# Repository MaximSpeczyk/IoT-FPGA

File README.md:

# Team-H
Advanced Embedded Systems: Smart Greenhouse (Mqtt server and multiple notes)

Hardware Engineering: Vending machine (PCB design, VHDL programm)

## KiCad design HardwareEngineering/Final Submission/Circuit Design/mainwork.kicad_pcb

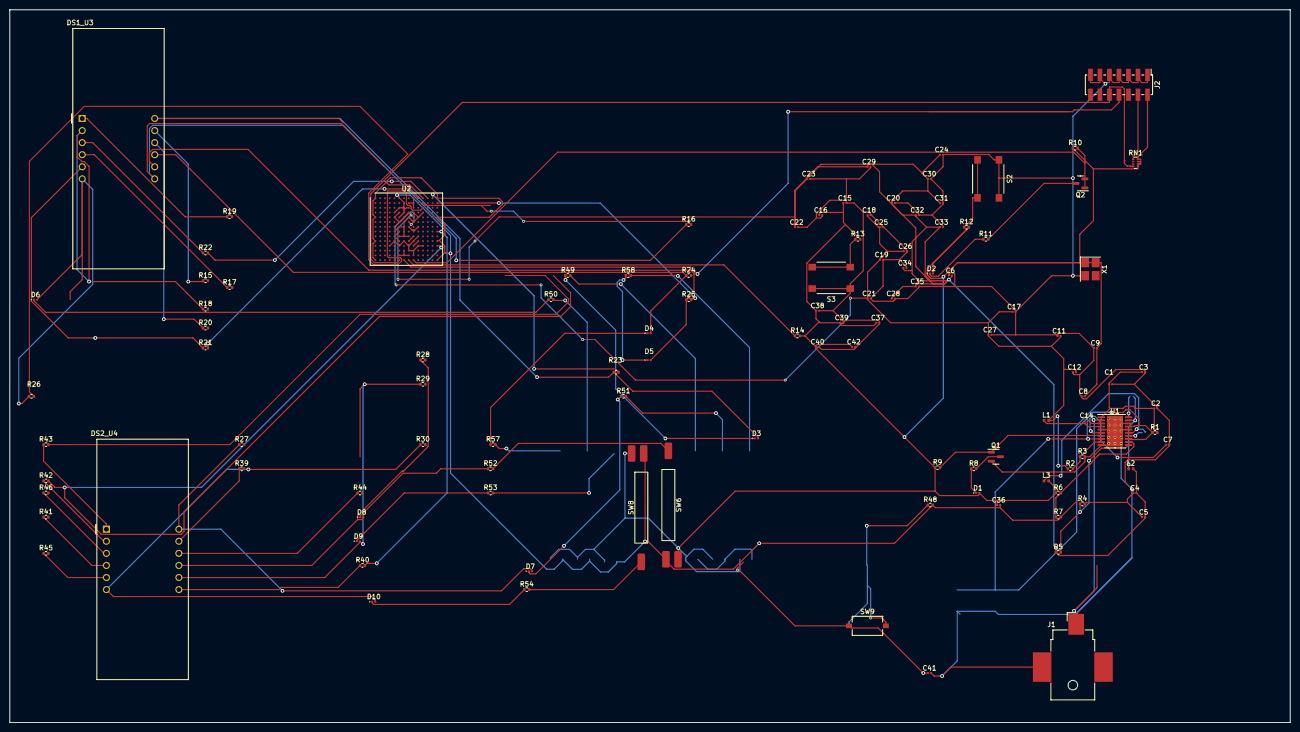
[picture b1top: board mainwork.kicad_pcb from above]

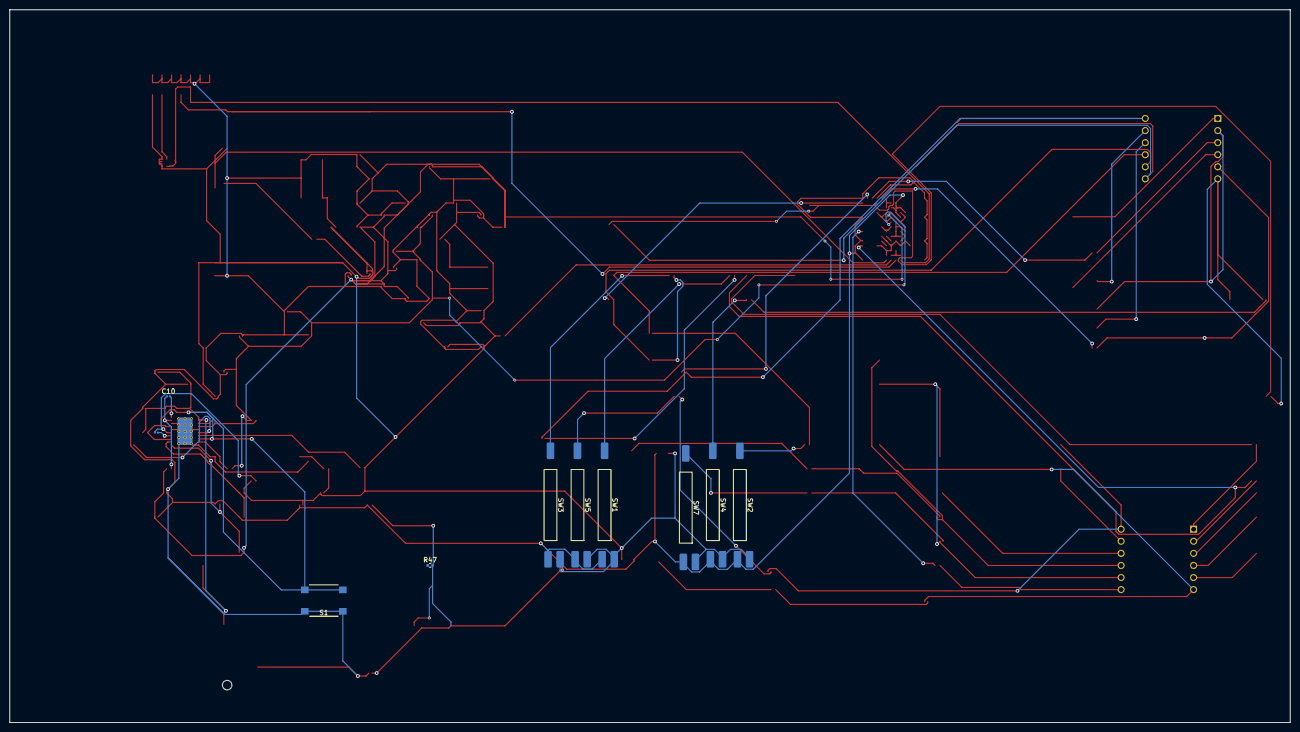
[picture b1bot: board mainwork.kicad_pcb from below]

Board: 2 copper layers, 269.2 x 149.9 mm, 125 parts (10 on the bottom side), 96 nets.

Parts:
C1, C2, C3: 10 µF; C_0201_0603Metric
C4, C5, C6, C8, C9, C11, C12: 22 µF; C_0201_0603Metric
C7: 1 µF; C_0201_0603Metric
C10, C13, C14, C15, C17, C18: 0.1 µF; C_0201_0603Metric
C16, C19, C20, C36: 47 µF; C_0201_0603Metric
C21, C22, C23, C24, C34, C37, C42: 4.7 µF; C_0201_0603Metric
C25, C26, C27, C28, C29, C30, C31, C32, C35, C38, C39, C40, C41: 0.47 µF; C_0201_0603Metric
C33: 100 µF; C_0201_0603Metric
D1, D2, D3, D4, D5, D6, D7, D8, D9, D10: LED; LED_0201_0603Metric
DS1_U3, DS2_U4: CA56-12CGKWA
J1: Barrel_Jack_Switch; BarrelJack_CUI_PJ-036AH-SMT_Horizontal
J2: XILINX_JTAG; PinHeader_2x07_P2.00mm_Vertical_SMD
L1, L3: 2.2 µH; L_0402_1005Metric
L2: 2.2 µF; L_0402_1005Metric
Q1, Q2: DMN2041L; SOT-23
R1, R9: 100K; R_0402_1005Metric
R2: 3.0K; R_0402_1005Metric
R3, R4, R7: 2.2K; R_0402_1005Metric
R5, R8, R11: 680; R_0402_1005Metric
R6: 7.36K; R_0402_1005Metric
R10, R15, R16, R17, R18, R19, R20, R21, R22, R23, R24, R25, R26, R27, R28, R29, R30, R39, R40, R41, R42, R43, R44, R45, R46, R47, R48, R49, R50, R51, R52, R53, R54, R57, R58: 330; R_0402_1005Metric
R12, R13, R14: 4.75K; R_0402_1005Metric
RN1: 10K; R_Array_Convex_4x0402
S1, S2, S3: B3FS_1010P
SW1, SW2, SW3, SW4, SW5, SW6, SW7, SW8: SW_Push_SPDT; SW_SPDT_REED_MSDM-DT
SW9: SW_SPST; SW_Tactile_SPST_NO_Straight_CK_PTS636Sx25SMTRLFS
U1: TPS65581; HTSSOP-20-1EP_4.4x6.5mm_P0.65mm_EP3.4x6.5mm_Mask2.75x3.43mm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
U2: XC7S50-FTGB196; Xilinx_FTGB196
X1: DSC61XX; Oscillator_SMD_Abracon_ASE-4Pin_3.2x2.5mm_HandSoldering

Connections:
+1V0: C4.2, C5.2, C6.2, C20.1, C22.1, C23.1, C24.1, C28.1, C29.1, C30.1, C31.1, C32.1, C33.1, C34.1, C35.1, L2.2, R5.1, U2.D6 (VCCINT), U2.D8 (VCCINT), U2.E5 (VCCBRAM), U2.E7 (VCCINT), U2.E9 (VCCINT), U2.F6 (VCCINT), U2.G5 (VCCBRAM), U2.G9 (VCCINT), U2.H6 (VCCINT), U2.J5 (VCCBRAM), U2.J9 (VCCINT), U2.K6 (VCCINT), U2.K8 (VCCINT)
+1V8A: C11.2, C12.2, C17.1, C18.1, C19.1, C21.1, C25.1, C26.1, C27.1, L1.2, R2.1, U2.F8 (VCCADC_0), U2.F10 (VCCAUX), U2.H8 (VREFP_0), U2.H10 (VCCAUX), U2.K10 (VCCAUX), U2.L9 (VCCAUX)
+3V3: C8.2, C9.2, C15.1, C16.1, C36.1, C37.1, C38.1, C39.1, C40.1, C41.1, C42.1, D1.2 (A), D2.2 (A), J2.2 (VREF), L3.2, R6.1, R9.1, R10.1, R12.2, R13.2, R14.2, RN1.5 (R4.2), RN1.6 (R3.2), RN1.7 (R2.2), RN1.8 (R1.2), SW1.1 (A), SW2.1 (A), SW3.1 (A), SW4.1 (A), SW5.1 (A), SW6.1 (A), SW7.1 (A), SW8.1 (A), SW9.1 (A), U2.G13 (VCCO_14), U2.K13 (VCCO_14), U2.M7 (M0_0), U2.N6 (VCCO_0), U2.N7 (CFGBVS_0), U2.N8 (VCCO_0), U2.N13 (VCCO_14), X1.1 (OE), X1.4 (VCC)
+12V: C1.1, C2.1, C3.1, J1.1, R1.2, U1.1 (VIN), U1.2 (VIN)
/Power Supply/PG00D: Q1.1 (G), R9.2, U1.7 (PG)
/Utilities/FPGA_DONE: Q2.1 (G), R10.2, U2.P9 (DONE_0)
/Utilities/INIT_B: R14.1, U2.P8 (INIT_B_0)
/Utilities/JTAG_TCK: J2.6 (TCK), RN1.2 (R2.1), U2.A7 (TCK_0)
/Utilities/JTAG_TDI: J2.10 (TDI), RN1.4 (R4.1), U2.P6 (TDO_0)
/Utilities/JTAG_TDO: J2.8 (TDO), RN1.3 (R3.1), U2.P7 (TDI_0)
/Utilities/JTAG_TMS: J2.4 (TMS), RN1.1 (R1.1), U2.M6 (TMS_0)
/Utilities/PROGRAM_B: R13.1, S3.3, S3.4, U2.L7 (PROGRAM_B_0)
/Vending Machine/DS1A: DS1_U3.11 (a), R15.1
/Vending Machine/DS1B: DS1_U3.7 (b), R16.1
/Vending Machine/DS1C: DS1_U3.4 (c), R17.1
/Vending Machine/DS1D: DS1_U3.2 (d), R18.1
/Vending Machine/DS1E: DS1_U3.1 (e), R19.1
/Vending Machine/DS1F: DS1_U3.10 (f), R20.1
/Vending Machine/DS1G: DS1_U3.5 (g), R21.1
/Vending Machine/DS1P: DS1_U3.3 (DPX), R22.1
/Vending Machine/DS2A: DS2_U4.11 (a), R39.1
/Vending Machine/DS2B: DS2_U4.7 (b), R40.1
/Vending Machine/DS2C: DS2_U4.4 (c), R41.1
/Vending Machine/DS2D: DS2_U4.2 (d), R42.1
/Vending Machine/DS2E: DS2_U4.1 (e), R43.1
/Vending Machine/DS2F: DS2_U4.10 (f), R44.1
/Vending Machine/DS2G: DS2_U4.5 (g), R45.1
/Vending Machine/DS2P: DS2_U4.3 (DPX), R46.1
/Vending Machine/DSCA1: D3.2 (A), DS1_U3.12 (CA1), R23.1
/Vending Machine/DSCA2: D4.2 (A), DS1_U3.9 (CA2), R24.1
/Vending Machine/DSCA3: D5.2 (A), DS1_U3.8 (CA3), R25.1
/Vending Machine/DSCA4: D6.2 (A), DS1_U3.6 (CA4), R26.1
/Vending Machine/DSCA5: D7.2 (A), DS2_U4.12 (CA1), R27.1
/Vending Machine/DSCA6: D8.2 (A), DS2_U4.9 (CA2), R28.1
/Vending Machine/DSCA7: D9.2 (A), DS2_U4.8 (CA3), R29.1
/Vending Machine/DSCA8: D10.2 (A), DS2_U4.6 (CA4), R30.1
/Vending Machine/EDS1A: R15.2, U2.E11 (IO_0_14)
/Vending Machine/EDS1B: R16.2, U2.B11 (IO_L1P_T0_D00_MOSI_14)
/Vending Machine/EDS1C: R17.2, U2.B12 (IO_L1N_T0_D01_DIN_14)
/Vending Machine/EDS1CA1: R23.2, U2.A13 (IO_L4N_T0_D05_14)
/Vending Machine/EDS1CA2: R24.2, U2.B13 (IO_L5P_T0_D06_14)
/Vending Machine/EDS1CA3: R25.2, U2.B14 (IO_L5N_T0_D07_14)
/Vending Machine/EDS1CA4: R26.2, U2.C11 (IO_L6P_T0_FCS_B_14)
/Vending Machine/EDS1D: R18.2, U2.D10 (IO_L2P_T0_D02_14)
/Vending Machine/EDS1E: R19.2, U2.C10 (IO_L2N_T0_D03_14)
/Vending Machine/EDS1F: R20.2, U2.B10 (IO_L3P_T0_DQS_PUDC_B_14)
/Vending Machine/EDS1G: R21.2, U2.A10 (IO_L3N_T0_DQS_EMCCLK_14)
/Vending Machine/EDS1P: R22.2, U2.A12 (IO_L4P_T0_D04_14)
/Vending Machine/EDS2A: R39.2, U2.H13 (IO_L14P_T2_SRCC_14)
/Vending Machine/EDS2B: R40.2, U2.H14 (IO_L14N_T2_SRCC_14)
/Vending Machine/EDS2C: R41.2, U2.M13 (IO_L15P_T2_DQS_RDWR_B_14)
/Vending Machine/EDS2CA5: R27.2, U2.C12 (IO_L6N_T0_D08_VREF_14)
/Vending Machine/EDS2CA6: R28.2, U2.F12 (IO_L7P_T1_D09_14)
/Vending Machine/EDS2CA7: R29.2, U2.E12 (IO_L7N_T1_D10_14)
/Vending Machine/EDS2CA8: R30.2, U2.D12 (IO_L8P_T1_D11_14)
/Vending Machine/EDS2D: R42.2, U2.L14 (IO_L15N_T2_DQS_DOUT_CSO_B_14)
/Vending Machine/EDS2E: R43.2, U2.L12 (IO_L16P_T2_CSI_B_14)
/Vending Machine/EDS2F: R44.2, U2.L13 (IO_L16N_T2_D31_14)
/Vending Machine/EDS2G: R45.2, U2.J11 (IO_L17P_T2_D30_14)
/Vending Machine/EDS2P: R46.2, U2.J12 (IO_L17N_T2_D29_14)
/Vending Machine/VendingMachineRESET: R47.1, U2.M10 (IO_25_14)
GND: C1.2, C2.2, C3.2, C4.1, C5.1, C6.1, C7.2, C8.1, C9.1, C11.1, C12.1, C15.2, C16.2, C17.2, C18.2, C19.2, C20.2, C21.2, C22.2, C23.2, C24.2, C25.2, C26.2, C27.2, C28.2, C29.2, C30.2, C31.2, C32.2, C33.2, C34.2, C35.2, C36.2, C37.2, C38.2, C39.2, C40.2, C41.2, C42.2, J1.2, J2.1 (GND), J2.3 (GND), J2.5 (GND), J2.7 (GND), J2.9 (GND), J2.11 (GND), J2.13 (GND), Q1.2 (S), Q2.2 (S), R3.2, R4.2, R7.2, R48.2, S1.1, S1.2, S2.1, S2.2, S3.1, S3.2, SW1.3 (C), SW2.3 (C), SW3.3 (C), SW4.3 (C), SW5.3 (C), SW6.3 (C), SW7.3 (C), SW8.3 (C), U1.5 (PGND1), U1.10 (GND), U1.16 (PGND3), U1.18 (PGND2), U1.21 (PAD), U2.A1 (GND), U2.A6 (GND), U2.A9 (GND), U2.A11 (GND), U2.A14 (GND), U2.B4 (GND), U2.B7 (GND), U2.B8 (VCCBATT_0), U2.B9 (GND), U2.C2 (GND), U2.C6 (GND), U2.C7 (GND), U2.C8 (GND), U2.C9 (GND), U2.C13 (GND), U2.D5 (GND), U2.D7 (GND), U2.D9 (GND), U2.D11 (GND), U2.E1 (GND), U2.E3 (GND), U2.E6 (GND), U2.E8 (GND), U2.E10 (GND), U2.E14 (GND), U2.F5 (GND), U2.F7 (GNDADC_0), U2.F9 (GND), U2.G3 (GND), U2.G6 (GND), U2.G7 (VREFN_0), U2.G8 (VP_0), U2.G10 (GND), U2.G12 (GND), U2.H5 (GND), U2.H7 (VN_0), U2.H9 (GND), U2.J6 (GND), U2.J7 (DXN_0), U2.J8 (DXP_0), U2.J10 (GND), U2.K1 (GND), U2.K5 (GND), U2.K7 (GND), U2.K9 (GND), U2.K14 (GND), U2.L4 (GND), U2.L6 (GND), U2.L8 (GND), U2.L10 (GND), U2.L11 (GND), U2.M8 (M1_0), U2.M9 (M2_0), U2.N3 (GND), U2.N5 (GND), U2.N9 (GND), U2.N12 (GND), U2.P1 (GND), U2.P14 (GND), X1.2 (GND)
unnamed: D1.1 (K), R8.1
unnamed: D2.1 (K), R11.1
unnamed: D3.1 (K), R49.1
unnamed: D4.1 (K), R57.1
unnamed: D5.1 (K), R58.1
unnamed: D6.1 (K), R50.1
unnamed: D7.1 (K), R51.1
unnamed: D8.1 (K), R52.1
unnamed: D9.1 (K), R53.1
unnamed: D10.1 (K), R54.1
unnamed: Q1.3 (D), R8.2
unnamed: Q2.3 (D), R11.2
unnamed: R49.2, SW1.2 (B)
unnamed: R57.2, SW2.2 (B)
unnamed: R58.2, SW3.2 (B)
unnamed: R50.2, SW4.2 (B)
unnamed: R51.2, SW5.2 (B)
unnamed: R52.2, SW6.2 (B)
unnamed: R53.2, SW7.2 (B)
unnamed: R54.2, SW8.2 (B)
unnamed: R47.2, R48.1, SW9.2 (B)
unnamed: R1.1, S1.3, S1.4, U1.8 (EN1), U1.13 (EN3), U1.17 (EN2)
unnamed: C14.1, L1.1, U1.4 (SW1)
unnamed: C10.1, L2.1, U1.19 (SW2)
unnamed: C13.1, L3.1, U1.15 (SW3)
unnamed: C14.2, U1.3 (VBST1)
unnamed: C10.2, U1.20 (VBST2)
unnamed: C13.2, U1.14 (VBST3)
unnamed: R2.2, R3.1, U1.9 (VFB1)
unnamed: R4.1, R5.2, U1.11 (VFB2)
unnamed: R6.2, R7.1, U1.12 (VFB3)
unnamed: C7.1, U1.6 (VREG5)
SYSCLK: U2.G11 (IO_L12P_T1_MRCC_14), X1.3 (OUT)
SYSRES: R12.1, S2.3, S2.4, U2.H11 (IO_L13P_T2_MRCC_14)

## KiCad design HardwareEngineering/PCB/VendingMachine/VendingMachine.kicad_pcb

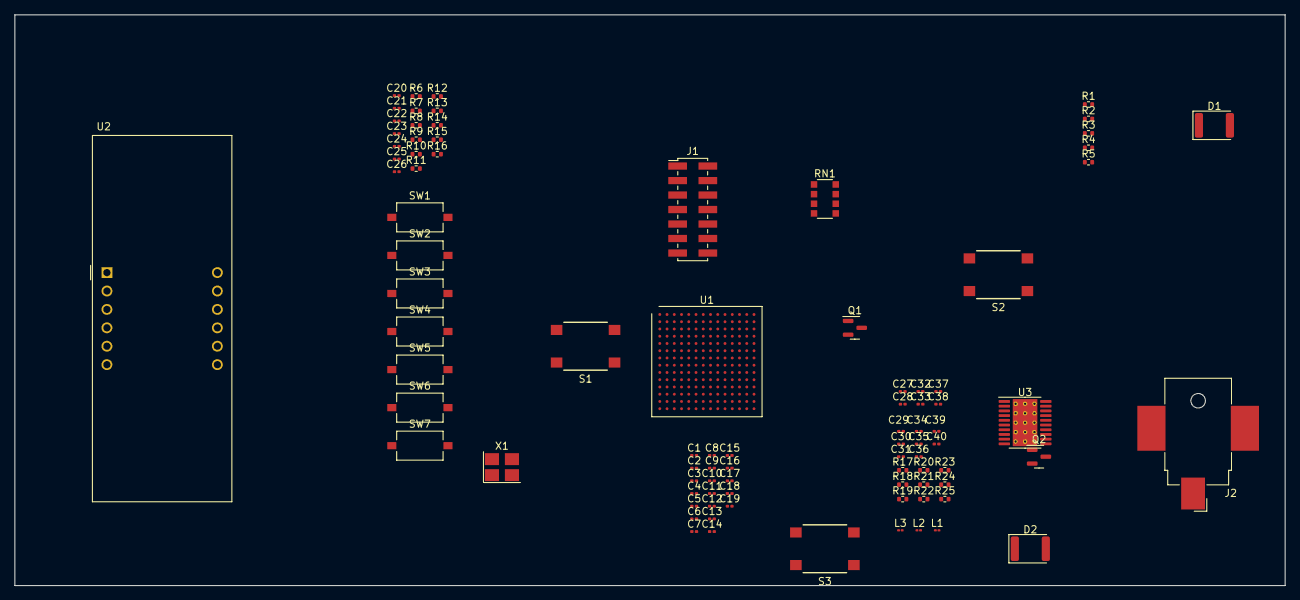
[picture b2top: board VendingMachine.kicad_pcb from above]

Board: 2 copper layers, 175.3 x 78.7 mm, 89 parts (0 on the bottom side), 64 nets, no tracks yet.

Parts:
C1, C2, C4, C7, C9, C17, C18, C20: 47 uF; C_0201_0603Metric
C3, C6, C10, C11, C12, C13, C14, C15, C16, C23, C24, C25, C26: 0.47 uF; C_0201_0603Metric
C5, C8, C31, C32, C33: 0.1 uF; C_0201_0603Metric
C19: 100 uF; C_0201_0603Metric
C21, C22: 4.7 uF; C_0201_0603Metric
C27, C28, C29: 10 uF; C_0201_0603Metric
C30: 1 uF; C_0201_0603Metric
C34, C35, C36, C37, C38, C39, C40: 22 uF; C_0201_0603Metric
D1: FPGA_DONE; LED_1812_4532Metric
D2: LED; LED_1812_4532Metric
J1: XILINX_JTAG; PinHeader_2x07_P2.00mm_Vertical_SMD
J2: Barrel_Jack_Switch; BarrelJack_CUI_PJ-036AH-SMT_Horizontal
L1, L2, L3: 2.2 uH; L_01005_0402Metric
Q1, Q2: DMN2041L; SOT-23
R1, R2: 4.75K; R_0402_1005Metric
R3, R5, R6, R7, R8, R9, R10, R11, R12, R13, R14, R15, R16: 330; R_0402_1005Metric
R4, R18, R22: 680; R_0402_1005Metric
R17: 100K; R_0402_1005Metric
R19: 100 K; R_0402_1005Metric
R20, R21, R23: 2.2 K; R_0402_1005Metric
R24: 7.36K; R_0402_1005Metric
R25: 3.0 K; R_0402_1005Metric
RN1: 10K; R_Array_Convex_4x1206
S1: CFG_RESET; B3FS_1010P
S2: SYS_RESET; B3FS_1010P
S3: B3FS_1010P
SW1, SW2, SW3, SW4, SW5, SW6, SW7: SW_SPST; SW_Tactile_SPST_NO_Straight_CK_PTS636Sx25SMTRLFS
U1: XC7S50-FTGB196; Xilinx_FTGB196
U2: CA56-12CGKWA
U3: TPS65581; HTSSOP-20-1EP_4.4x6.5mm_P0.65mm_EP3.4x6.5mm_Mask2.75x3.43mm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
X1: DSC61XX; Oscillator_SMD_Abracon_ASE-4Pin_3.2x2.5mm_HandSoldering

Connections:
+1V0: C4.2, C9.2, C11.2, C12.2, C13.2, C14.2, C15.2, C16.2, C17.2, C18.2, C19.2, C34.1, C36.1, C39.1, L2.2, R22.1, U1.D6 (VCCINT), U1.D8 (VCCINT), U1.E5 (VCCBRAM), U1.E7 (VCCINT), U1.E9 (VCCINT), U1.F6 (VCCINT), U1.G5 (VCCBRAM), U1.G9 (VCCINT), U1.H6 (VCCINT), U1.J5 (VCCBRAM), U1.J9 (VCCINT), U1.K6 (VCCINT), U1.K8 (VCCINT)
+1V8A: C5.2, C8.2, C38.1, C40.1, L3.2, R25.1, U1.F8 (VCCADC_0), U1.H8 (VREFP_0)
+3.3V: C20.1, C21.1, C22.1, C23.1, C24.1, C25.1, C26.1, U1.G13 (VCCO_14), U1.K13 (VCCO_14), U1.N13 (VCCO_14)
+3V3: C7.2, C35.1, C37.1, D1.2 (A), J1.2 (VREF), L1.2, R1.1, R2.1, R3.1, R5.1, R24.1, RN1.5 (R4.2), RN1.6 (R3.2), RN1.7 (R2.2), RN1.8 (R1.2), U1.M7 (M0_0), U1.N6 (VCCO_0), U1.N7 (CFGBVS_0), U1.N8 (VCCO_0), X1.1 (OE), X1.4 (VCC)
+12V: J2.1, R19.2
/power Supply/PGOOD: Q2.1 (G), R17.2, U3.7 (PG)
/vendingUtilities/FPGA_DONE: Q1.1 (G), R3.2, U1.P9 (DONE_0)
/vendingUtilities/INIT_B: R1.2, U1.P8 (INIT_B_0)
/vendingUtilities/JTAG_TCK: J1.6 (TCK), RN1.2 (R2.1), U1.A7 (TCK_0)
/vendingUtilities/JTAG_TDI: J1.10 (TDI), RN1.4 (R4.1), U1.P7 (TDI_0)
/vendingUtilities/JTAG_TDO: J1.8 (TDO), RN1.3 (R3.1), U1.P6 (TDO_0)
/vendingUtilities/JTAG_TMS: J1.4 (TMS), RN1.1 (R1.1), U1.M6 (TMS_0)
/vendingUtilities/PROGRAM_B: R2.2, S1.1, S1.2, U1.L7 (PROGRAM_B_0)
GND: C1.1, C2.1, C3.1, C4.1, C5.1, C6.1, C7.1, C8.1, C9.1, C10.1, C11.1, C12.1, C13.1, C14.1, C15.1, C16.1, C17.1, C18.1, C19.1, C20.2, C21.2, C22.2, C23.2, C24.2, C25.2, C26.2, C27.1, C28.1, C29.1, C30.1, C34.2, C35.2, C36.2, C37.2, C38.2, C39.2, C40.2, J1.1 (GND), J1.3 (GND), J1.5 (GND), J1.7 (GND), J1.9 (GND), J1.11 (GND), J1.13 (GND), J2.2, Q2.2 (S), R20.2, R21.2, R23.2, S2.3, S2.4, S3.1, S3.2, U1.A1 (GND), U1.A6 (GND), U1.A9 (GND), U1.A11 (GND), U1.A14 (GND), U1.B4 (GND), U1.B7 (GND), U1.B8 (VCCBATT_0), U1.B9 (GND), U1.C2 (GND), U1.C6 (GND), U1.C7 (GND), U1.C8 (GND), U1.C9 (GND), U1.C13 (GND), U1.D5 (GND), U1.D7 (GND), U1.D9 (GND), U1.D11 (GND), U1.E1 (GND), U1.E3 (GND), U1.E6 (GND), U1.E8 (GND), U1.E10 (GND), U1.E14 (GND), U1.F5 (GND), U1.F7 (GNDADC_0), U1.F9 (GND), U1.G3 (GND), U1.G6 (GND), U1.G7 (VREFN_0), U1.G8 (VP_0), U1.G10 (GND), U1.G12 (GND), U1.H5 (GND), U1.H7 (VN_0), U1.H9 (GND), U1.J6 (GND), U1.J7 (DXN_0), U1.J8 (DXP_0), U1.J10 (GND), U1.K1 (GND), U1.K5 (GND), U1.K7 (GND), U1.K9 (GND), U1.K14 (GND), U1.L4 (GND), U1.L6 (GND), U1.L8 (GND), U1.L10 (GND), U1.L11 (GND), U1.M8 (M1_0), U1.M9 (M2_0), U1.N3 (GND), U1.N5 (GND), U1.N9 (GND), U1.N12 (GND), U1.P1 (GND), U1.P14 (GND), U3.5 (PGND1), U3.10 (GND), U3.16 (PGND3), U3.18 (PGND2), U3.21 (PAD), X1.2 (GND)
unnamed: C1.2, C2.2, C3.2, C6.2, C10.2, U1.F10 (VCCAUX), U1.H10 (VCCAUX), U1.K10 (VCCAUX), U1.L9 (VCCAUX)
unnamed: C27.2, C28.2, C29.2, U3.1 (VIN), U3.2 (VIN)
unnamed: D1.1 (K), R4.1
unnamed: D2.2 (A), R17.1
unnamed: D2.1 (K), R18.1
unnamed: Q1.3 (D), R4.2
unnamed: Q2.3 (D), R18.2
unnamed: S1.3, S1.4
unnamed: SW1.1 (A), U2.4 (c)
unnamed: R16.2, SW1.2 (B)
unnamed: SW2.1 (A), U2.7 (b)
unnamed: R6.2, SW2.2 (B)
unnamed: SW3.1 (A), U2.11 (a)
unnamed: R7.2, SW3.2 (B)
unnamed: SW4.1 (A), U2.10 (f)
unnamed: R13.2, SW4.2 (B)
unnamed: SW5.1 (A), U2.1 (e)
unnamed: R14.2, SW5.2 (B)
unnamed: SW6.1 (A), U2.2 (d)
unnamed: R15.2, SW6.2 (B)
unnamed: SW7.1 (A), U2.5 (g)
unnamed: R12.2, SW7.2 (B)
unnamed: R12.1, U1.E11 (IO_0_14)
unnamed: R14.1, U1.B12 (IO_L1N_T0_D01_DIN_14)
unnamed: R13.1, U1.B11 (IO_L1P_T0_D00_MOSI_14)
unnamed: R16.1, U1.C10 (IO_L2N_T0_D03_14)
unnamed: R15.1, U1.D10 (IO_L2P_T0_D02_14)
unnamed: R7.1, U1.A10 (IO_L3N_T0_DQS_EMCCLK_14)
unnamed: R6.1, U1.B10 (IO_L3P_T0_DQS_PUDC_B_14)
unnamed: R8.1, U1.A13 (IO_L4N_T0_D05_14)
unnamed: R10.1, U1.B14 (IO_L5N_T0_D07_14)
unnamed: R9.1, U1.B13 (IO_L5P_T0_D06_14)
unnamed: R11.1, U1.C11 (IO_L6P_T0_FCS_B_14)
unnamed: R8.2, U2.12 (CA1)
unnamed: R9.2, U2.9 (CA2)
unnamed: R10.2, U2.8 (CA3)
unnamed: R11.2, U2.6 (CA4)
unnamed: R19.1, S3.3, S3.4, U3.8 (EN1), U3.13 (EN3), U3.17 (EN2)
unnamed: C33.2, L3.1, U3.4 (SW1)
unnamed: C32.2, L2.1, U3.19 (SW2)
unnamed: C31.2, L1.1, U3.15 (SW3)
unnamed: C33.1, U3.3 (VBST1)
unnamed: C32.1, U3.20 (VBST2)
unnamed: C31.1, U3.14 (VBST3)
unnamed: R23.1, R25.2, U3.9 (VFB1)
unnamed: R20.1, R22.2, U3.11 (VFB2)
unnamed: R21.1, R24.2, U3.12 (VFB3)
unnamed: C30.2, U3.6 (VREG5)
SYSCLK: U1.G11 (IO_L12P_T1_MRCC_14), X1.3 (OUT)
SYSRES: R5.2, S2.1, S2.2, U1.H11 (IO_L13P_T2_MRCC_14)

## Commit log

2023-04-27 Create Folders and Readmes
2023-05-04 Connecting Arduino with Hotspot
    Connecting Arduino with Hotspot from Phone
2023-05-04 Add task 1 and manage the folders
2023-05-04 Adding Lab 1
    HalfAdder and FullAdder, plus their test bench.
2023-05-04 DecoderBit
    DecoderBit
2023-05-04 FourBitFullAdder
2023-05-04 changing names
2023-05-04 DecoderBit_tb
2023-05-04 Changing name
2023-05-04 Creating web server with humidity and temperture data
2023-05-04 renaming
2023-05-10 Create Cad for One Bit Adder
2023-05-10 Create #auto_saved_files#
2023-05-10 Create Block_diagram
2023-05-10 Add files via upload
    The diagram give an overview of the entire System, with all components connection
2023-05-11 File Management
2023-05-15 Create Folder
2023-05-23 Rename
2023-06-01 Block Diagram Vending Machine
    Concept of the Vending Machine.
2023-06-06 Sensor Data
    All the sensor and actuator datasheets
2023-06-11 machine Digram concept
2023-06-12 This is just an initial code i understood
2023-06-15 Create adafruitIO.py
    DRAFT (not complete/working)
2023-06-15 PCB Design
2023-06-15 Update arduinoMQTTPublisher.ino
    Comments to understand the code better
2023-06-15 Update arduinoMQTTSubcriber.ino
    Add comments
2023-06-15 misplacement
2023-06-15 VDHL IMplementation
2023-06-15 FPGA Implementation
2023-06-15 Manage
    Delete one obsolete folder.
2023-06-15 3D and PCB
2023-06-15 Manage files
2023-06-15 Update state machine
2023-06-17 refined draft
2023-06-22 Debugged1
    VHDL and ViVado files
2023-06-22 Presentation
2023-06-22 refined files
    Vhdl, vivado and pressentation
2023-07-11 Final Submission
2023-07-11 PCB Schematic
2023-07-11 3D PCB View
2023-07-11 Hardware pptx
2023-07-11 FPGA
2023-07-11 Vending Machine Test Bench.
    Note: The clock just keeps running.
2023-07-12 vending vhd code
2023-07-12 Added working Video to presentation
2023-07-12 video added
